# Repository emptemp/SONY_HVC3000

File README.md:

all the stuff regarding sony hvc3000 "handy"cam.

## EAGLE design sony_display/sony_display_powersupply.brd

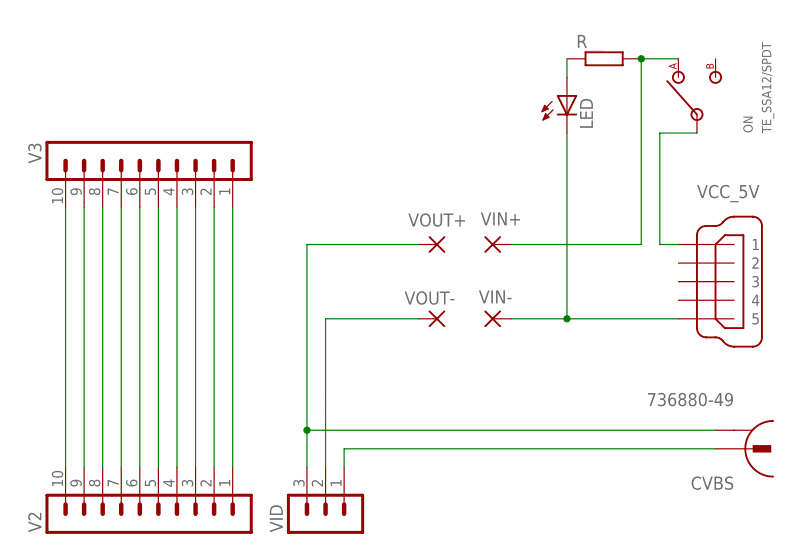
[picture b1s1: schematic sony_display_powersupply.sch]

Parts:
CVBS: 736880-49
LED: LED3MM
ON: TE_SSA12/SPDT
R__: R-EU_M0805; M0805
V2, V3: MA10-1
VCC_5V: MINI-USB-32005-301; 32005-301
VID: MA03-1
VIN+: 2,54/1,0
VIN-: 2,54/1,0
VOUT+: 2,54/1,0
VOUT-: 2,54/1,0

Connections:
unnamed: V2.10, V3.10
unnamed: V2.9, V3.9
unnamed: V2.8, V3.8
unnamed: V2.7, V3.7
unnamed: V2.1, V3.1
unnamed: V2.2, V3.2
unnamed: V2.3, V3.3
unnamed: V2.5, V3.5
unnamed: V2.4, V3.4
unnamed: V2.6, V3.6
unnamed: ON.IN, VCC_5V.1
unnamed: LED.K (C), VCC_5V.5, VIN-.1
unnamed: VID.2, VOUT-.1
unnamed: CVBS.1, VID.1
unnamed: CVBS.2, VID.3, VOUT+.1
unnamed: ON.1 (A), R__.2, VIN+.1
unnamed: LED.A, R__.1

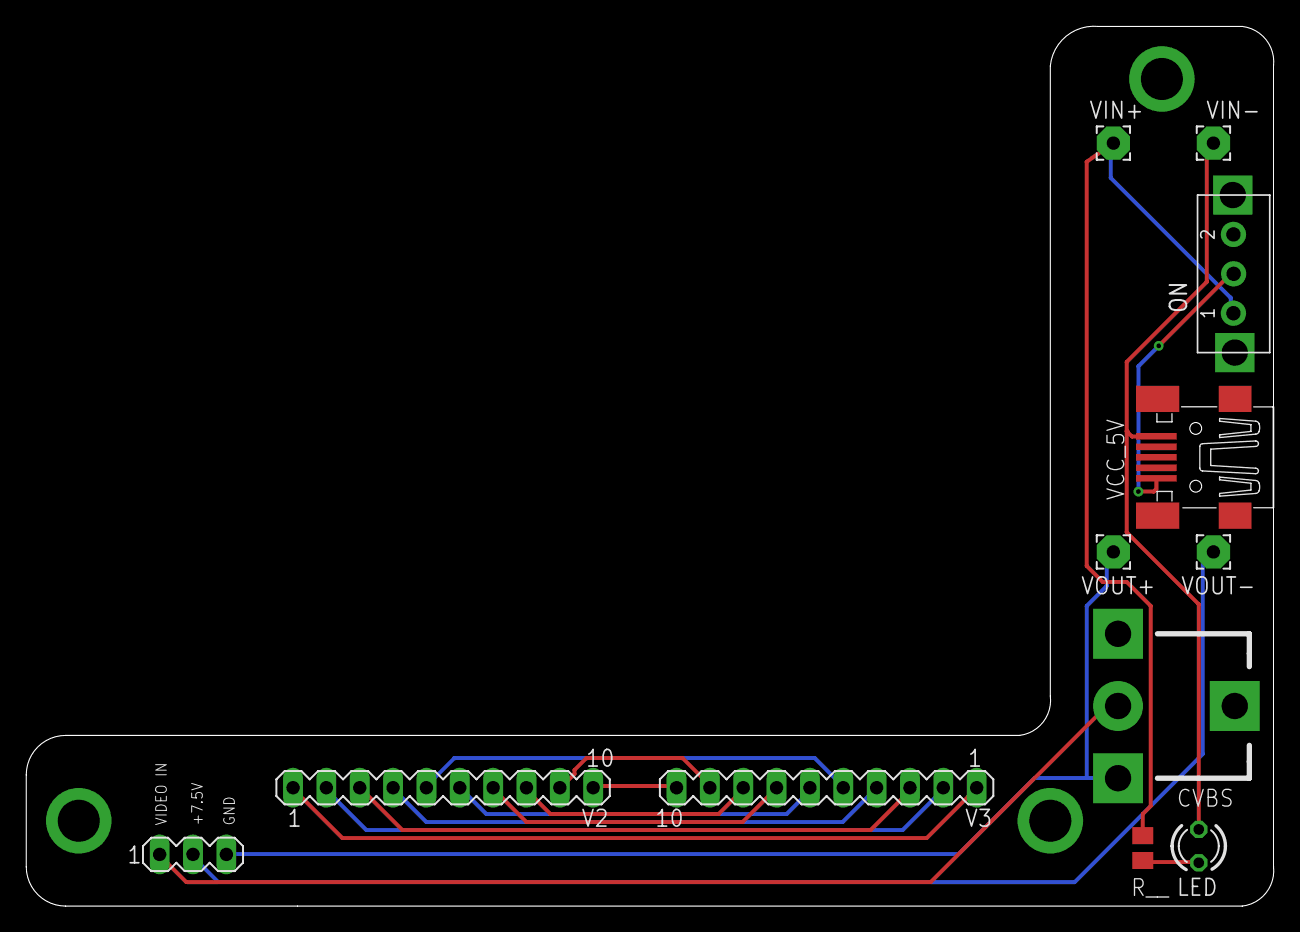
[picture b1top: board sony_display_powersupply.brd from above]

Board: 2 copper layers, 95.0 x 67.0 mm, 12 parts (0 on the bottom side), 17 nets.

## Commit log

2020-03-28 initial commit, almost lost it
